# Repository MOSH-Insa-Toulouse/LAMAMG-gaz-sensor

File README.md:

# LAMAMG-gaz-sensor

> A Smart Gaz Sensor that just works.

[![Node-Red Version][node-red-image]][node-red-url]
[![Node-Red-Dashboard Version][node-red-dashboard-image]][node-red-dashboard-url]
[![Node-Red-TTN Version][node-red-ttn-image]][node-red-ttn-url]
[![Arduino-TTN Version][arduino-ttn-image]][arduino-ttn-url]

The result of our project can be seen on the following picture, which is a screenshot of our application's dashboard.

Our application is simple:
- we collect data through a gaz sensor connected to an Arduino board
- then, we send it to a NodeRed serving using TTN and LoRa
- once the data is received by the server, the dashboard is updated
- the values are displayed separately (two gauges for the sensor & the button state values, one chart for the evolution of the sensor value)

As of now, the button is purely decorative (it once served to send data when at '1').   

We designed our own Arduino shield using the KiCad software. It directly connects to the Arduino board used (101). 
On it, you can add the following devices:
- a Grove LCD screen (http://wiki.seeedstudio.com/Grove-LCD_RGB_Backlight)
- a Grove gaz sensor (http://wiki.seeedstudio.com/Grove-Gas_Sensor)
- our homemade gaz sensor (with an integrated AOP)
- the RN2483 LoRa transceiver module and its board (https://www.microchip.com/wwwproducts/en/RN2483) 

## Installation

OS X & Linux:

```bash
sudo apt install nodejs npm
npm install node-red node-red-ttn node-red-dashboard
cp NodeRED/flows.json ~/.node-red/flows.json
node-red &
```

Then the Dashboard will be visible on http://localhost:1880/ui, and the admin page
will be available on http://localhost:1880.

## Usage example

Power up the Arduino next to a LoRa Gateway which is using The Things Network.
Then connect to http://localhost:1880/ui on the device running Node-Red, and watch
the gauges and the graphs updated in real-time.

## Dependencies

* Node-RED
    * node-red
    * node-red-dashboard
    * node-red-contrib-ttn
* TTN - The Things Network Account
* Arduino
    * Arduino Compiler
    * The Things Network Library
    * Software Serial Library

## Development setup

### NodeRED
Follow the Instllation section, and visit the http://localhost:1880/ with your
favorite browser. You can here change the flows linked to the Dashboard.
Please update the default NodeRED flow to `~/path/to/directory/NodeRED/flows.json`
into the `~/.node-red/settings.json` file before modifying the flows.

### KiCad
The PCB has been designed on KiCad. To contribute to it, you should install it on
[here](http://kicad-pcb.org/download/).
You will then find the KiCad project into the `Kicad/shield` directory.

### Arduino code
The Arduino Code has been developped on _Arduino IDE_ which can be
downloaded [here](https://www.arduino.cc/en/Main/Software). You may need
to fix the dependencies you'll find in the Dependencies' section.
You can easily find them into the package manager of the IDE.

## Contributors
 
 | Name           | Contact                        |
 |----------------|--------------------------------|
 | Maxime Grac    | grac@etud.insa-toulouse.fr     |
 | Lucas Audibert | l_audibe@etud.insa-toulouse.fr |
 | Adrien Marty   | a_marty@etud.insa-toulouse.fr  |

Distributed under the MIT license. See ``LICENSE`` for more information.

## Contributing

1. Fork it (https://github.com/MOSH-Insa-Toulouse/LAMAMG-gaz-sensor.git)
2. Create your feature branch (`git checkout -b feature/fooBar`)
3. Commit your changes (`git commit -am 'Add some fooBar'`)
4. Push to the branch (`git push origin feature/fooBar`)
5. Create a new Pull Request

<!-- Markdown link & img dfn's -->
[node-red-image]: https://img.shields.io/badge/node--red-v0.19.5-orange.svg
[node-red-url]: https://nodered.org
[node-red-dashboard-image]: https://img.shields.io/badge/node--red--dashboard-v2.9.8-orange.svg
[node-red-dashboard-url]: https://github.com/node-red/node-red-dashboard
[node-red-ttn-image]: https://img.shields.io/badge/node--red--ttn-v2.0.4-orange.svg
[node-red-ttn-url]: https://www.npmjs.com/package/node-red-contrib-ttn
[arduino-ttn-image]: https://img.shields.io/badge/TTN_Arduino-v2.5.13-orange.svg
[arduino-ttn-url]: https://github.com/TheThingsNetwork/arduino-device-lib

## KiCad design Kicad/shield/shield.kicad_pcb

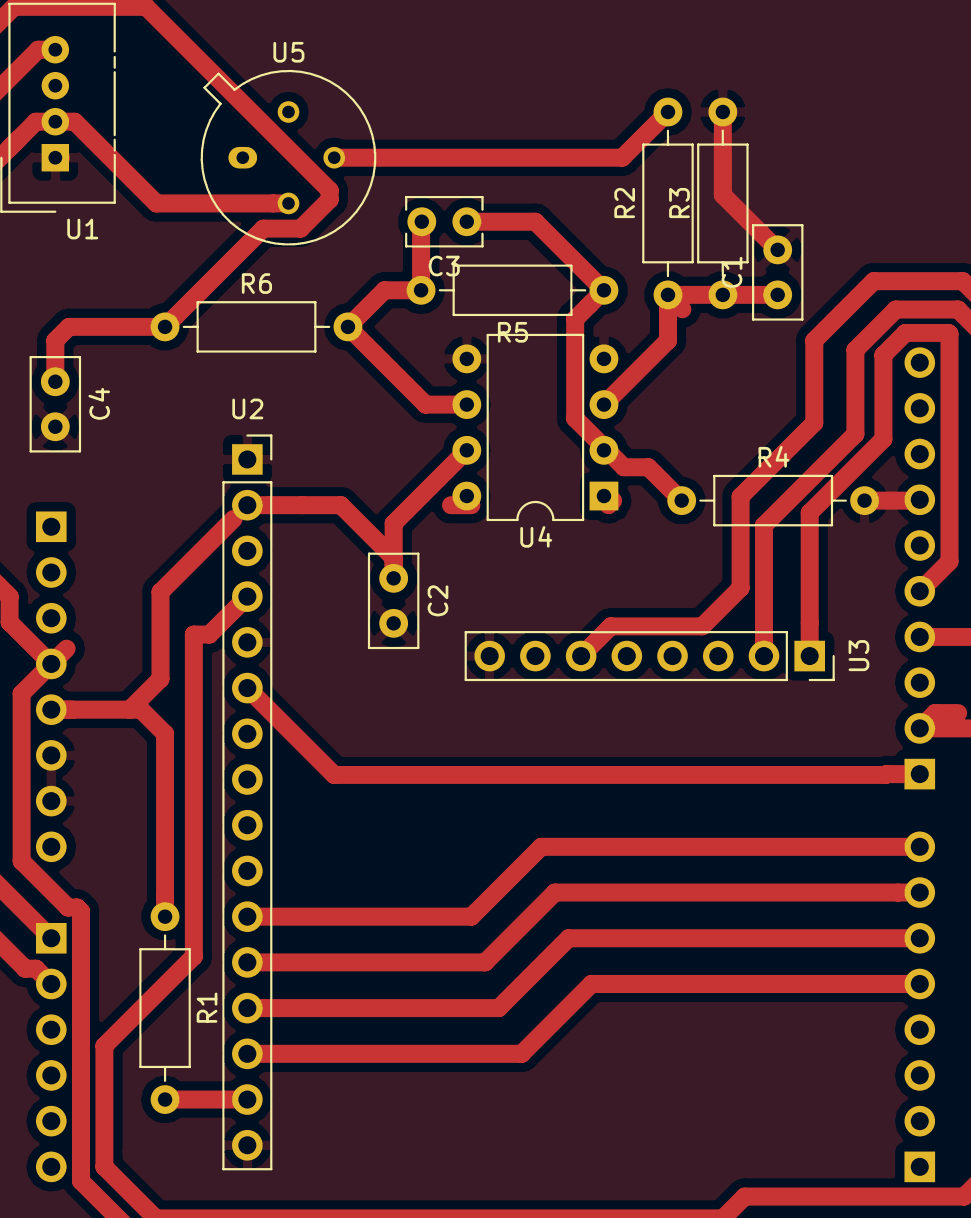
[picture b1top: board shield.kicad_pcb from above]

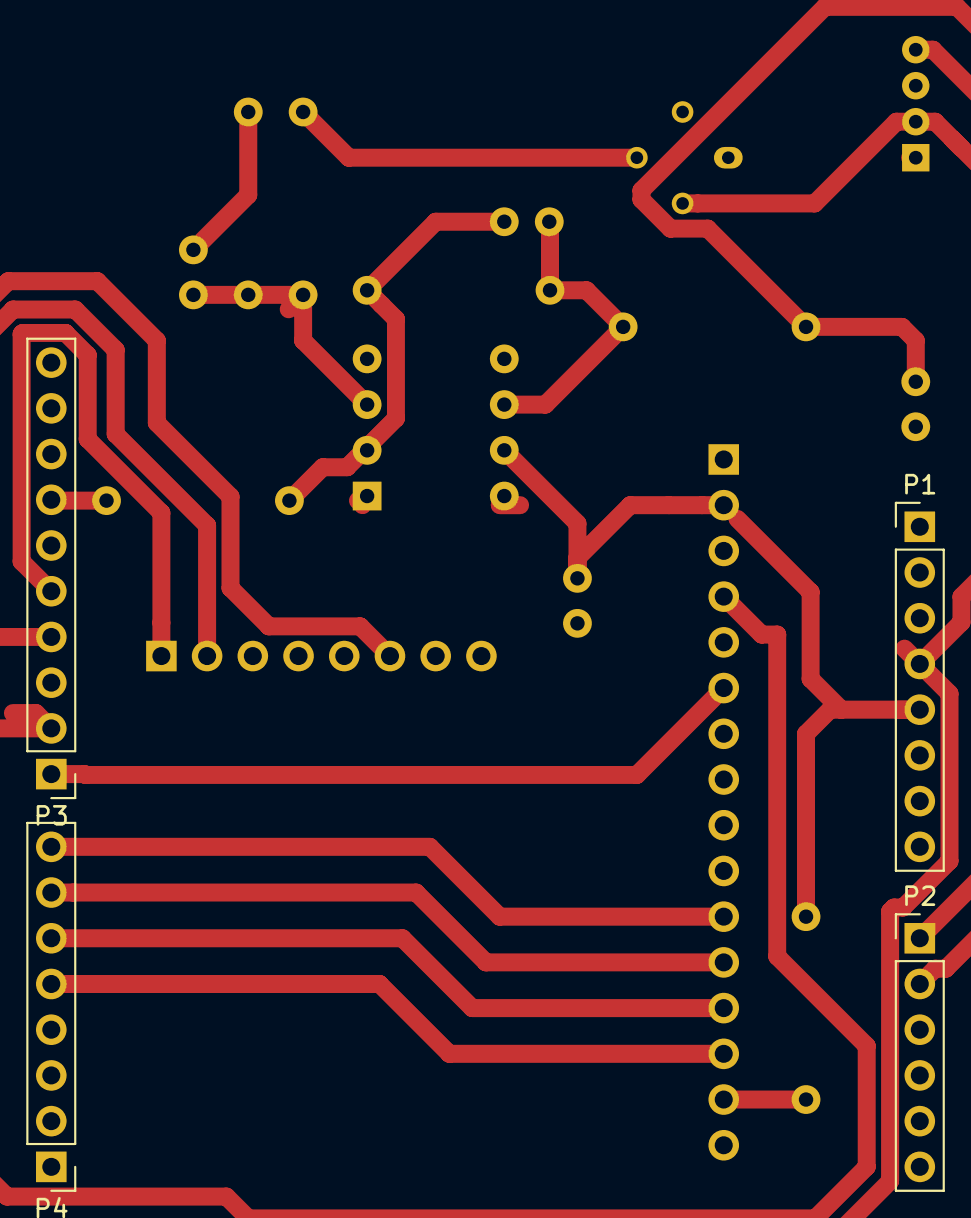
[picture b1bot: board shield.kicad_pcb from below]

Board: 2 copper layers, 19 parts (4 on the bottom side), 18 nets.

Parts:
C1, C2, C4: C; C_Disc_D5.0mm_W2.5mm_P2.50mm
C3: C; C_Rect_L4.0mm_W2.5mm_P2.50mm
P1, P4: CONN_01X08; PinHeader_1x08_P2.54mm_Vertical
P2: CONN_01X06; PinHeader_1x06_P2.54mm_Vertical
P3: CONN_01X10; PinHeader_1x10_P2.54mm_Vertical
R1, R2, R3, R4, R5, R6: R; R_Axial_DIN0207_L6.3mm_D2.5mm_P10.16mm_Horizontal
U1: gaz_sensor; NS-Tech_Grove_1x04_P2mm_Vertical
U2: LCD_screen; PinSocket_1x16_P2.54mm_Vertical
U3: RN2483A; PinSocket_1x08_P2.54mm_Vertical
U4: LT1050; DIP-8_W7.62mm
U5: Gaz_Sensor; TO-5-4

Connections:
+3V3: P1.4, U1.2, U3.6, U5.2
+5V: C2.1, P1.5, R1.1, U2.2, U4.7
/#D5: P4.6, U2.13
/#D6: P4.7, U2.12
/#D9: P3.2, U2.4
/#D11: P3.4, U3.2
/A0: P2.1, U1.4
/A1: C4.1, P2.2, R6.1
/D4: P4.5, U2.14
/D7: P4.8, U2.11
/D8: P3.1, U2.6
/D12: P3.5, U3.1
/Isens: R2.2, U5.3
GND: C1.2, C2.2, C4.2, P1.6, P1.7, P3.7, R3.2, R4.2, U1.1, U2.1, U2.5, U2.16, U3.8, U4.4, U4.5
unnamed: C1.1, R2.1, R3.1, U4.3
unnamed: C3.1, R4.1, R5.1, U4.2
unnamed: C3.2, R5.2, R6.2, U4.6
unnamed: R1.2, U2.15

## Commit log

2018-10-09 First commit Arduino
2018-10-16 Send data over Lora
2018-10-16 Ajout Kicad
2018-10-16 Add Node-Red flow for Dashboard
2018-10-16 Ajout elements
2018-10-18 Creation PCB
2018-10-29 modification shield
2018-11-28 Add `screenshot.png` file
2018-11-28 Added changes to the markdown (mostly description of the application)
2018-11-28 Adding `screenshot_kicad.png` file
2018-11-29 récupération des fichiers KiCad
2018-11-29 Modification du readme
2018-11-29 Resolving connection problems between grounds
2018-11-29 Fix no saving
2018-11-29 Modification du screenshot 3D KiCad
2018-11-29 Ajout de commentaires dans le code arduino
